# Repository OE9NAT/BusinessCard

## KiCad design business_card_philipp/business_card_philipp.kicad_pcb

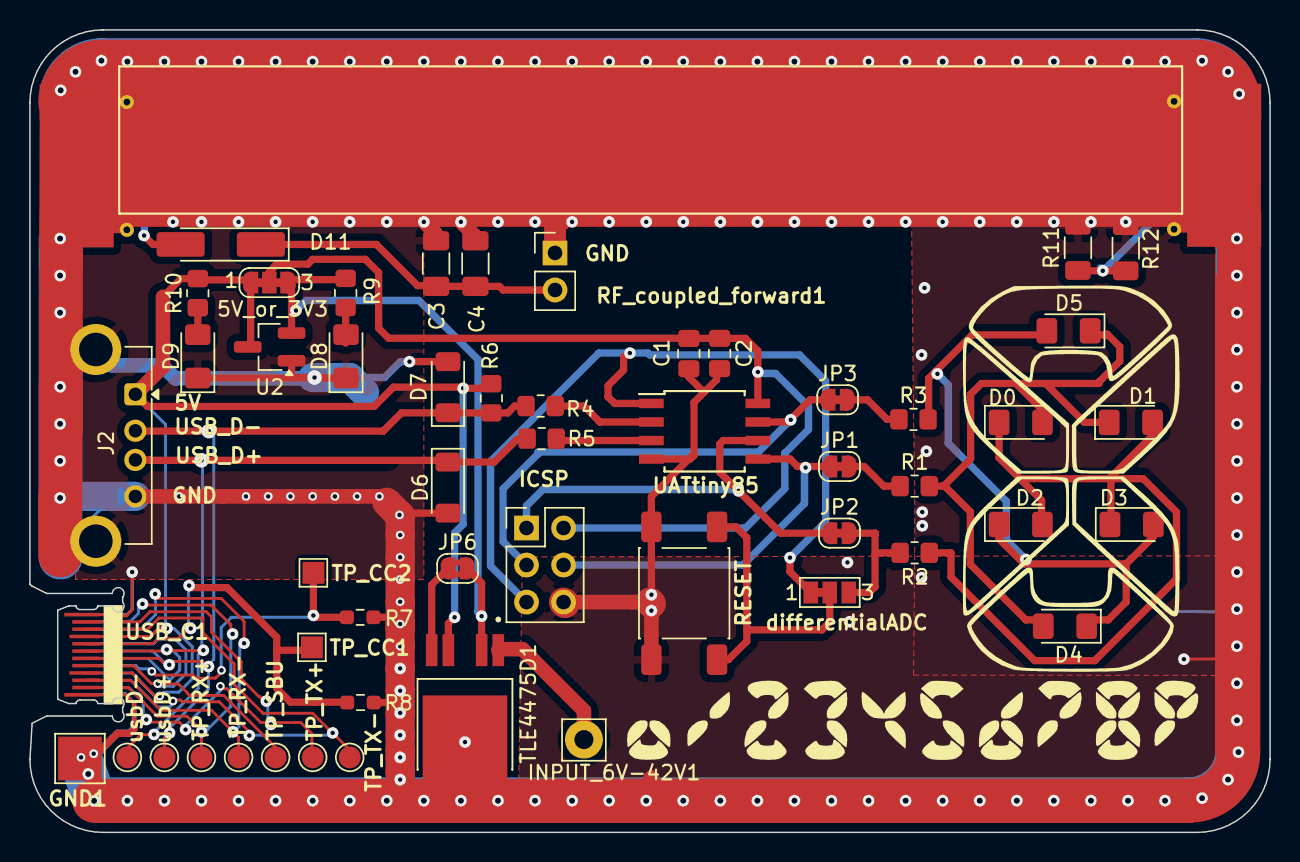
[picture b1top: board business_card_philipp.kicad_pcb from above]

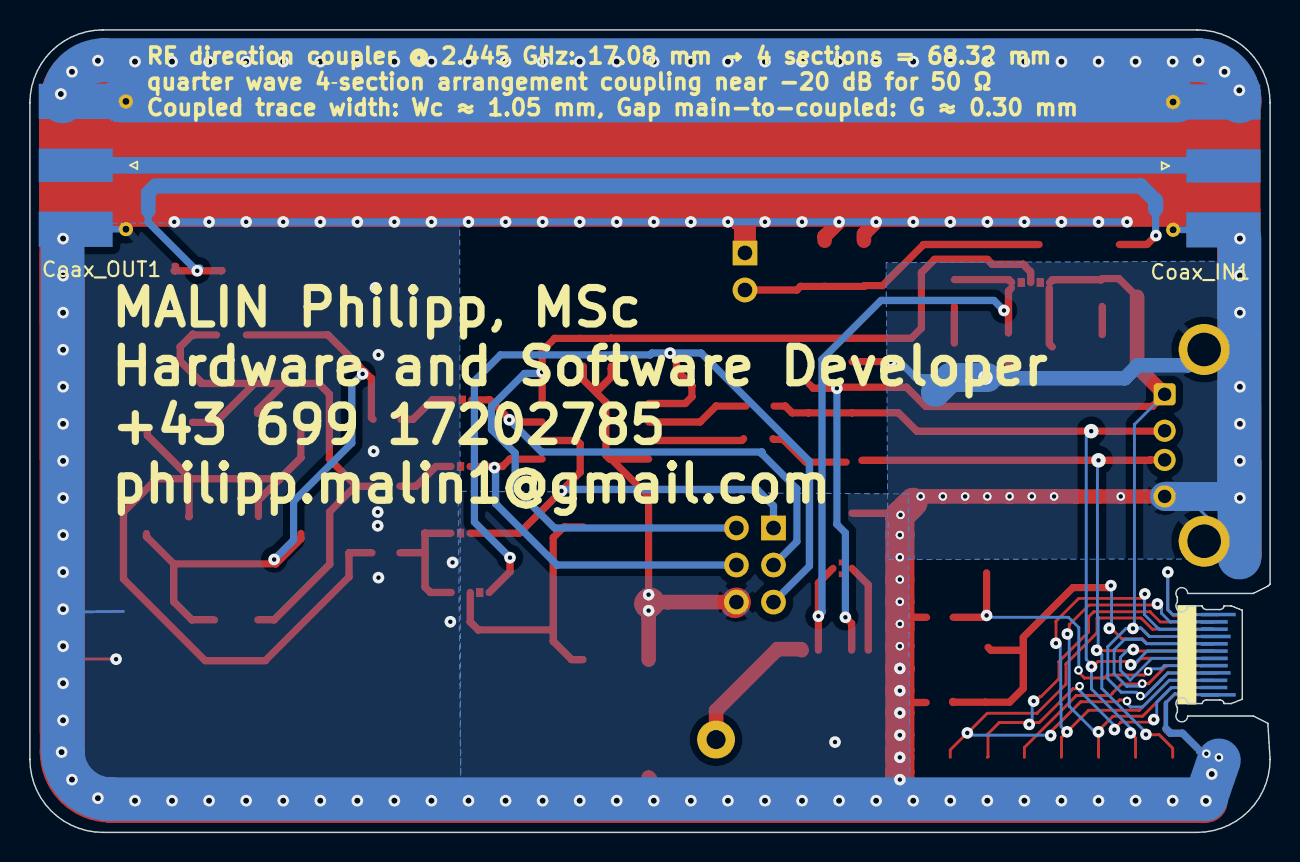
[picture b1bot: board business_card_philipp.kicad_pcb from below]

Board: 2 copper layers, 85.0 x 55.0 mm, 55 parts (2 on the bottom side), 33 nets.

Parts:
5V_or_3V3: Bridge_jumper 5V to 3V3; SolderJumper-3_P1.3mm_Bridged123_RoundedPad1.0x1.5mm_Number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
 : LOGO
C1: 1µ; C_0805_2012Metric_Pad1.18x1.45mm_HandSolder
C2: 100n; C_0805_2012Metric_Pad1.18x1.45mm_HandSolder
C3, C4: C; C_1206_3216Metric_Pad1.33x1.80mm_HandSolder
Coax_IN1: Conn_Coaxial_Small; SMA_Molex_73251-1153_EdgeMount_Horizontal
Coax_OUT1: Conn_Coaxial_Small; SMA_Molex_73251-1153_EdgeMount_Horizontal
D0: LED red ~660nm; LED_1206_3216Metric_Pad1.42x1.75mm_HandSolder
D1: LED green ~550nm; LED_1206_3216Metric_Pad1.42x1.75mm_HandSolder
D2, D3, D4, D5: LED; LED_1206_3216Metric_Pad1.42x1.75mm_HandSolder
D6, D7: 3V3; D_MiniMELF
D8: LED 3V3; LED_1206_3216Metric_Pad1.42x1.75mm_HandSolder
D9: LED 5V; LED_1206_3216Metric_Pad1.42x1.75mm_HandSolder
D11: LL4448; D_MiniMELF_Handsoldering
GND1: TP0; TestPoint_Pad_3.0x3.0mm
ICSP: Conn_02x03; PinHeader_2x03_P2.54mm_Vertical
INPUT_6V-42V1: INPUT_<42V; Pin_D1.3mm_L11.3mm_W2.8mm_Flat
J2: USB_A; USB_A_Connfly_DS1095
JP1: Pin_PB0; SolderJumper-2_P1.3mm_Bridged_RoundedPad1.0x1.5mm
JP2: Pin_PB1; SolderJumper-2_P1.3mm_Bridged_RoundedPad1.0x1.5mm
JP3: Pin_PB3; SolderJumper-2_P1.3mm_Bridged_RoundedPad1.0x1.5mm
JP6: Q2_enable_5V; SolderJumper-2_P1.3mm_Bridged2Bar_RoundedPad1.0x1.5mm
R1, R2, R3, R9, R10: 1k; R_0805_2012Metric_Pad1.20x1.40mm_HandSolder
R4, R5: 68; R_0805_2012Metric_Pad1.20x1.40mm_HandSolder
R6: 1k5; R_0805_2012Metric_Pad1.20x1.40mm_HandSolder
R7, R8: 5k1; R_0603_1608Metric_Pad0.98x0.95mm_HandSolder
R11, R12: 100; R_1206_3216Metric_Pad1.30x1.75mm_HandSolder
RESET: SW_MEC_5E; SW_Push_1P1T_NO_E-Switch_TL3301NxxxxxG
RF_coupled_forward1: Conn_01x02_Pin; PinHeader_1x02_P2.54mm_Vertical
TLE4475D1: TLE4476DXT; TO114P998X235-5
TP_CC1, TP_CC2: TestPoint; TestPoint_Pad_1.5x1.5mm
TP_RX+: TP4; TestPoint_Pad_D1.5mm
TP_RX-: TP5; TestPoint_Pad_D1.5mm
TP_SBU: TP12; TestPoint_Pad_D1.5mm
TP_TX+: TP_TX+; TestPoint_Pad_D1.5mm
TP_TX-: TP10; TestPoint_Pad_D1.5mm
U2: AP2125N-3.3TRG1; SOT-23_Handsoldering
UATtiny85: ATtiny85-20S; SOIC-8W_5.3x5.3mm_P1.27mm
USB_C1: ÚSB-C edge_connector; PCBTypeC_24P
differentialADC: JP5; SolderJumper-3_P1.3mm_Bridged12_Pad1.0x1.5mm_NumberLabels
usbD+: TP1; TestPoint_Pad_D1.5mm
usbD-: TP2; TestPoint_Pad_D1.5mm

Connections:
+3V3: 5V_or_3V3.3 (B), JP6.2 (B), R9.2, TLE4475D1.2 (Q1), U2.2 (VO)
+5V: 5V_or_3V3.1 (A), J2.1 (VBUS), R6.1, R10.2, TLE4475D1.4 (Q2), U2.3 (VI), USB_C1.A4 (VBUS), USB_C1.A9 (VBUS), USB_C1.B4 (VBUS), USB_C1.B9 (VBUS)
/ADC1: ICSP.3, JP3.1 (A), UATtiny85.7 (PB2)
/usb D+: R5.2, UATtiny85.3 (XTAL2/PB4)
/usb D-: R4.2, UATtiny85.2 (XTAL1/PB3)
D+ usb: D6.1 (K), J2.3 (D+), R5.1, USB_C1.A6 (DP1), USB_C1.B6 (DP2), usbD-.1
D- usb: D7.1 (K), J2.2 (D-), R4.1, R6.2, USB_C1.A7 (DN1), USB_C1.B7 (DN2), usbD+.1
GND: C1.2, C2.2, C3.2, C4.2, Coax_IN1.2 (Ext), Coax_OUT1.2 (Ext), D6.2 (A), D7.2 (A), D8.1 (K), D9.1 (K), GND1.1, ICSP.6, J2.4 (GND), J2.5 (Shield), R7.2, R8.2, R11.2, R12.2, RESET.2, RF_coupled_forward1.1, TLE4475D1.3 (GND), U2.1 (GND), UATtiny85.4 (GND), USB_C1.A1 (GND), USB_C1.A12 (GND), USB_C1.B1 (GND), USB_C1.B12 (GND)
unnamed: 5V_or_3V3.2 (C), C1.1, C2.1, ICSP.2, UATtiny85.8 (VCC)
unnamed: Coax_IN1.1 (In), Coax_OUT1.1 (In)
unnamed: D0.2 (A), D1.1 (K), D4.2 (A), D5.1 (K), R1.2
unnamed: D0.1 (K), D1.2 (A), D2.2 (A), D3.1 (K), R2.1
unnamed: D2.1 (K), D3.2 (A), D4.1 (K), D5.2 (A), R3.2
unnamed: D8.2 (A), R9.1
unnamed: D9.2 (A), R10.1
unnamed: D11.2 (A), R11.1, R12.1
unnamed: C3.1, C4.1, D11.1 (K), RF_coupled_forward1.2
unnamed: ICSP.1, JP2.1 (A), UATtiny85.6 (PB1)
unnamed: ICSP.4, JP1.1 (A), UATtiny85.5 (AREF/PB0)
unnamed: ICSP.5, UATtiny85.1 (~RESET/PB5), differentialADC.1 (A)
unnamed: JP1.2 (B), R1.1
unnamed: JP2.2 (B), R2.2, differentialADC.3 (B)
unnamed: JP3.2 (B), R3.1
unnamed: JP6.1 (A), TLE4475D1.5 (EN)
unnamed: INPUT_6V-42V1.1, TLE4475D1.1 (I)
unnamed: R8.1, TP_CC1.1, USB_C1.A5 (CC1)
unnamed: R7.1, TP_CC2.1, USB_C1.B5 (CC2)
unnamed: RESET.1, differentialADC.2 (C)
RX+: TP_RX+.1, USB_C1.A11 (RXP2), USB_C1.B11 (RXP1)
RX-: TP_RX-.1, USB_C1.A10 (RXN2), USB_C1.B10 (RXN1)
SBU: TP_SBU.1, USB_C1.A8 (SBU1), USB_C1.B8 (SBU2)
TX+: TP_TX+.1, USB_C1.A2 (TXP1), USB_C1.B2 (TXP2)
TX-: TP_TX-.1, USB_C1.A3 (TXN1), USB_C1.B3 (TXN2)

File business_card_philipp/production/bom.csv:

Designator,Footprint,Quantity,Value,LCSC Part #
ATTINY85,SOIC-8W_5.3x5.3mm_P1.27mm,1,ATtiny85-20S,
C1,0805,1,1µ,
C2,0805,1,100n,
"C3, C4",1206,2,C,
"COAX_IN1, COAX_OUT1",SMA_Molex_73251-1153_EdgeMount_Horizontal,2,Conn_Coaxial_Small,
D0,1206,1,LED red ~660nm,
D1,1206,1,LED green ~550nm,
D11,D_MiniMELF_Handsoldering,1,LL4448,
"D2, D3, D4, D5",1206,4,LED,
"D6, D7",0805,2,3V3,
D8,1206,1,LED 3V3,
D9,1206,1,LED 5V,
GND,TestPoint_Pad_3.0x3.0mm,1,TP0,
ICSP,PinHeader_2x03_P2.54mm_Vertical,1,Conn_02x03_Odd_Even,
INPUT_6V-42V,Pin_D1.3mm_L11.3mm_W2.8mm_Flat,1,INPUT_<42V,
"R1, R10, R2, R3, R9",0805,5,1k,
"R11, R12",1206,2,100,
"R4, R5",0805,2,68,
R6,0805,1,1k5,
"R7, R8",0603,2,5k1,
RESET,SW_Push_1P1T_NO_E-Switch_TL3301NxxxxxG,1,SW_MEC_5E,
RF_COUPLED_FOWARD_OUT,PinHeader_1x02_P2.54mm_Vertical,1,Conn_01x02_Pin,
TLE4476D,TO114P998X235-5,1,TLE4476DXT,
"TP_CC1, TP_CC2",TestPoint_Pad_1.5x1.5mm,2,TestPoint,
TP_RX+,TestPoint_Pad_D1.5mm,1,TP4,
TP_RX-,TestPoint_Pad_D1.5mm,1,TP5,
TP_SBU,TestPoint_Pad_D1.5mm,1,TP12,
TP_TX+,TestPoint_Pad_D1.5mm,1,TP_TX+,
TP_TX-,TestPoint_Pad_D1.5mm,1,TP10,
U2,SOT-23_Handsoldering,1,AP2125N-3.3TRG1,
USB,USB_A_Connfly_DS1095,1,USB_A,
USBD+,TestPoint_Pad_D1.5mm,1,TP1,
USBD-,TestPoint_Pad_D1.5mm,1,TP2,

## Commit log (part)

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2025-12-21 setup project
    first try of a buissnescard in PCB format
2025-12-21 setup project
    first steps of setting up the project
2025-12-21 cleanup
2025-12-21 Add documentation, update .gitignore, and clean backups
    Added READNE.md with project overview and gitignore recommendations. Updated .gitignore to exclude KiCad backup and cache files. Removed several large backup zip files. Updated KiCad project files an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
2025-12-21 notes
    website docu
2025-12-24 doc
    documentation and specifing
2025-12-29 schematic update
    PCB placemnet of first components
2025-12-30 routing
2026-01-03 update tle4476D
2026-01-03 USB cand power routing
2026-01-04 direction coupler
    implementing and routing of RF direction coupler
2026-01-06 routing and backplane
2026-01-06 corrections and upload
2026-01-06 screenshot
2026-01-15 software number
    program the microcontroller to sow the numbers.
2026-01-16 pinout ICSP
